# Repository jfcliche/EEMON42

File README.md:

# EEMON42
ESP32-C3-based 42-channel home energy monitor using the Analog Device ADE7816 emergy monitor chip

Features

  - 42 Current monitoring inputs with 3.5 mm jacks for current transformers
  - Single board, 10x10 cm design with OLED screen with a OLED/switch/rotary encoder user interface
  - Two AC voltage for split phase voltage monitoring and board powering
  - Micropython control software with MQTT telemetry streamed over WiFi

# Status

  V0 Hardware
    - Board is built. 
    - Hardware validation:
      - Switcher works. Board can be powered via USB or AC jacks. 
      - Can operate the ESP32 via the USB and micropython. 
      - All buttons work.
      - OLED display works
      - Only one ADE7816 is populated so far, but we can read registers.
    - Todo: 
      - Check analog inputs of ADE7816. Populate rest of the board. Calibrate all inputs.

  Software
    - Building basic micropyton modules
    - Todo: 
      - Implement main loop and monitoring/GUI tasks as coroutines. Improve display functions. Integrate with Home Assistant.

# Design Details:
- Accurate Energy monitoring performed by seven ADE7816
  - ESP32-C3 controller implemented with a Espressif ESP32-C3-WROOM-02 or AI Thinker ESP-C3-13 module, providing 
      - Single core RISC-V 160 MHz processor
      - 4 MB flash
      - Wifi, Bluetooth
      - Embedded USB controller
  - 96x64 pixel, 0.96" OLED display
  - 3 pushbutton keys 
  - Rotary encoder with integrated push button
  - Dual 9-15VAC inputs for line voltage monitoring and powering the board
  - Micro-USB connector for UART programming and JTAG debugging, and alternate board powering      
  - Integrated DC-DC converter for wide input voltage range

# Rationale

The EEMON42 was developed as personal project for learning all the steps to build an embedded controller project from A to Z, starting from from schematics & layout, online PCB manufacturing, hand soldering of high density SMD devices, an developing the embedded controller software. More specifically, this includes:

   - Learn KiCAD 6.0 and learn to place and route designs
   - Use PCBWay or JLCPCB to manufacture the PCB
   - Learn SMD soldering techniques for sizes down to 0603 and QFN 0.5mm pitch devices
   - Learn the internal architecture of the ESP32-C3-based module
   - Software development tools (Visual Studio Code / Platform IO / ESP IDF/ Micropython etc)

# History

2022/06: Design start
2022/12: Board was manufactured by PCBJLC. Board is assembled. Preliminary hardware verification is performed: power, ESP32, buttons and OLED display works with Micropython. Discovered bug in esptool that prevent the flashing stub to operate when USB-enabled micropython has booted first.
2023/03: ADE7816 is installed. Successful communication with it. Implement Python object for it. Implement SPI object to handle SPI CS pins shared with buttons and pin interrupts.

# Known bugs & gotcha's:

v1 hardware:
  - GPIO9 can be pull down and prevent micropython boot if encoder is left in mid-position
  - Missing GPIO2 & GPIO8 pullup (but still works without those)
  - A reset switch would be nice, but is becoming les and less necessary as hardware matures
  - A power LED would prevent accidental soldering on a powered board...
  - Pad and copper pour cleareaces too small close to USB connector: rookie solderers might cause shorts when applying too much solder...
  - serial number chip (or some GPIO strapping) might be useful for software to identify the hardware automatically. rev2 GPIOs assignments will change.  
  - encoder is a bit too close to screen for big fingers. Buttons should be spread out more.
  - Find socket with proper height for screen.

# Changelog:

 v2 hardware (under development):
  - OLED CS7 is now on FSPICS0 for native hardware-enabled CS toggling (if possible)
  - Encoder Button CS2 is on GPIO9 to prevent unwanted boot mode and allow user-controlled to force downnloader boot (although USB interface does not need it except for esptool bug)
  - CS0 and CS1 moved to other GPIOs
  - Added weak pullups on GPIO2 and GPIO8 to be sure

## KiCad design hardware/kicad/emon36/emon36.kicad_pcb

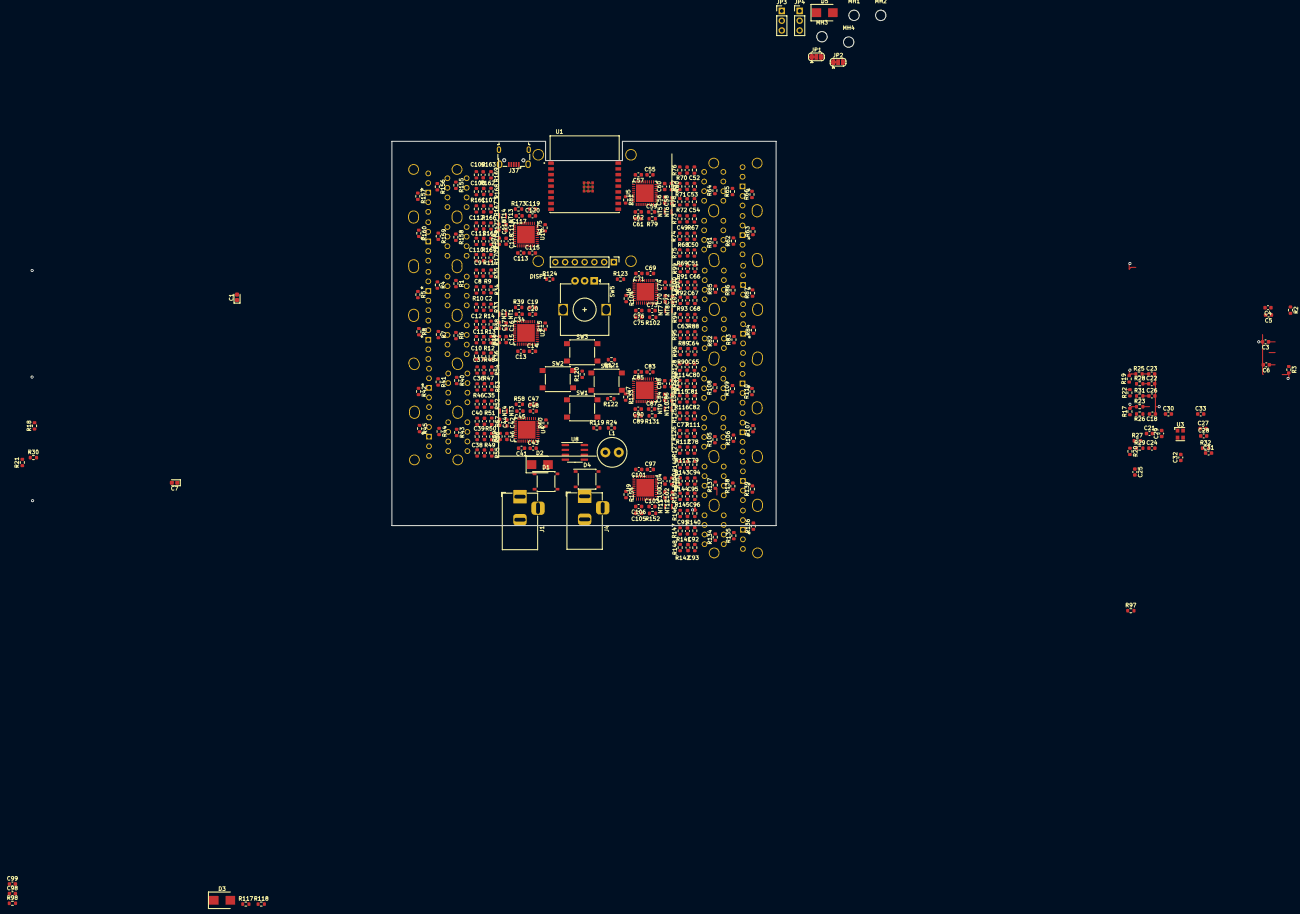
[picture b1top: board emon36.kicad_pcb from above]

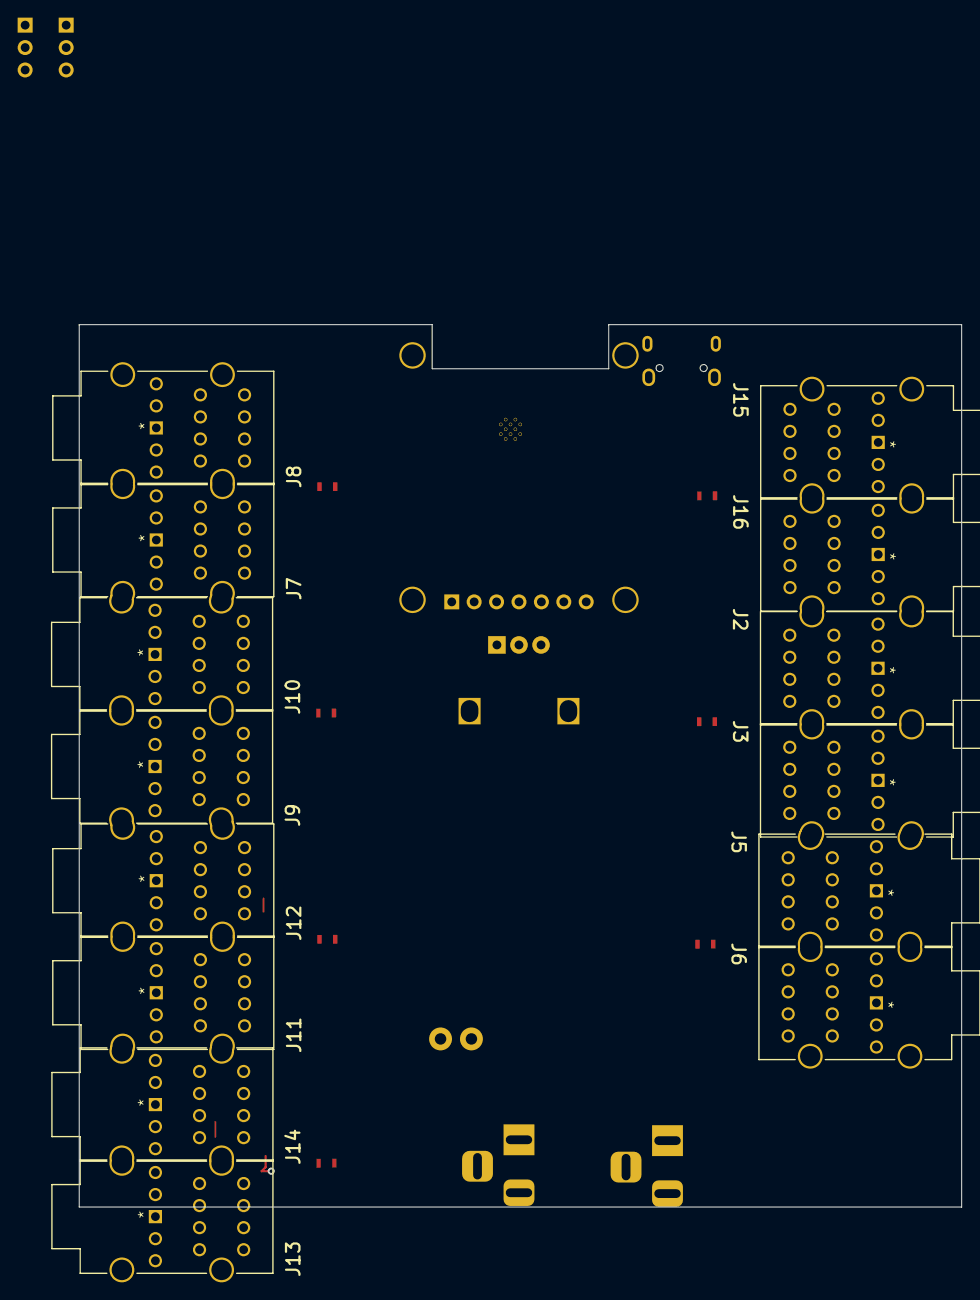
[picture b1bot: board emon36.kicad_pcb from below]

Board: 4 copper layers, 100.0 x 100.0 mm, 356 parts (14 on the bottom side), 197 nets.

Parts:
C1: 680uF/35V; CP_EIA-1608-08_AVX-J
C2, C8, C9, C10, C11, C12, C15, C34, C35, C36, C37, C38, C39, C40, C45, C46, C49, C50, C51, C52, C53, C54, C59, C60, C63, C64, C65, C66, C67, C68, C73, C74, C77, C78, C79, C80, C81, C82, C87, C88, C91, C92, C93, C94, C95, C96, C103, C104, C107, C108, C109, C110, C111, C112, C117, C118: 22nF; C_0603_1608Metric
C3, C6: 10uF/25V; C_0603_1608Metric
C4: 2.2nF; C_0603_1608Metric
C5, C18, C21, C22, C23, C26, C27, C28, C29: 10nF; C_0603_1608Metric
C7: 220uF/25V; CP_EIA-1608-08_AVX-J
C13, C16, C19, C24, C41, C42, C47, C55, C56, C61, C69, C70, C75, C83, C84, C89, C97, C100, C105, C113, C114, C119: 4.7uF; C_0603_1608Metric
C14, C20, C25, C43, C48, C57, C62, C71, C76, C85, C90, C101, C106, C115, C120: 0.22uF; C_0603_1608Metric
C17, C44, C58, C72, C86, C102, C116: 0.1uF; C_0603_1608Metric
C30, C31, C32, C33: 1uF/35V; C_0603_1608Metric
C98, C99: 22pF; C_0603_1608Metric
D1, D4: ABS6; Diode_Bridge_Diotec_ABS
D2, D3, D5: B240; D_SMB
DISP1: SSD1331_RGB_OLED_94x64; SSD1331_RGB_OLED_96x64
J1, J4: Barrel_Jack; BarrelJack_Horizontal
J2, J3, J5, J6, J7, J8, J9, J10, J11, J12, J13, J14, J15, J16: STX-4335-5BGP-S1; STX-4335-5BGP-S1_KYC
J37: USB_B_Micro; USB_Micro-B_Wuerth_629105150521
JP1, JP2: SolderJumper_3_Bridged12; SolderJumper-3_P1.3mm_Bridged12_RoundedPad1.0x1.5mm
JP3, JP4: Jumper_3_Bridged12; PinHeader_1x03_P2.54mm_Vertical
L1: 82uH; L_Radial_D7.5mm_P3.50mm_Fastron_07P
MH1, MH2, MH3, MH4: MountingHole; MountingHole_2.7mm_M2.5
NT1, NT2, NT3, NT4, NT5, NT6, NT7, NT8, NT9, NT10, NT11, NT12, NT13, NT14: NetTie_2; NetTie-2_SMD_Pad0.5mm
R1, R4, R5, R6, R7, R8, R40, R41, R42, R43, R44, R45, R61, R62, R63, R64, R65, R66, R82, R83, R84, R85, R86, R87, R105, R106, R107, R108, R109, R110, R134, R135, R136, R137, R138, R139, R155, R156, R157, R158, R159, R160: RB; R_0603_1608Metric
R2, R97, R98: 0; R_0603_1608Metric
R3: 47k; R_0603_1608Metric
R9, R10, R11, R12, R13, R14, R16, R39, R46, R47, R48, R49, R50, R51, R58, R59, R67, R68, R69, R70, R71, R72, R79, R80, R88, R89, R90, R91, R92, R93, R102, R103, R111, R112, R113, R114, R115, R116, R131, R132, R140, R141, R142, R143, R144, R145, R152, R153, R161, R162, R163, R164, R165, R166, R173, R174: 1k; R_0603_1608Metric
R15, R60, R81, R104, R133, R154, R175: 22; R_0603_1608Metric
R17, R18, R19, R20, R21, R22, R117, R118: 75; R_0603_1608Metric
R23: 2.2K; R_0603_1608Metric
R24, R119, R120, R121, R122, R123, R124: 2.2k; R_0603_1608Metric
R25, R26, R27, R28: 21.5K; R_0603_1608Metric
R29, R30, R31, R32, R33, R34, R35, R36, R37, R38, R52, R53, R54, R55, R56, R57, R73, R74, R75, R76, R77, R78, R94, R95, R96, R99, R100, R101, R125, R126, R127, R128, R129, R130, R146, R147, R148, R149, R150, R151, R167, R168, R169, R170, R171, R172: 499; R_0603_1608Metric
SW1, SW2, SW3, SW4: SW_MEC_5E; SW_Push_1P1T_NO_6x6mm_H13mm
SW5: RotaryEncoder; RotaryEncoder_Alps_EC12E_Vertical_H20mm
U1: ESP32-C3-WROOM-02-N4; MODULE_ESP32-C3-WROOM-02-H4
U2, U4, U5, U6, U7, U9, U10: QFN-40-1EP_6x6mm_P0.5mm_EP4.6x4.6mm
U3: 16.384MHz; Oscillator_SMD_Kyocera_KC2520Z-4Pin_2.5x2.0mm
U8: TPS54233; SOIC-8_3.9x4.9mm_P1.27mm

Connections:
3V3: C7.1, C24.1, C25.1, D5.2 (A), DISP1.2 (VCC), J37.1 (VBUS), L1.2, R23.1, U1.1 (3V3), U2.2 (PULL_HIGH), U2.26 (VDD), U3.4 (VCC), U4.2 (PULL_HIGH), U4.26 (VDD), U5.2 (PULL_HIGH), U5.26 (VDD), U6.2 (PULL_HIGH), U6.26 (VDD), U7.2 (PULL_HIGH), U7.26 (VDD), U8.5 (FB), U9.2 (PULL_HIGH), U9.26 (VDD), U10.2 (PULL_HIGH), U10.26 (VDD)
/CH0/IABC_N: C107.2, C108.2, C109.2, J15.1, NT13.1, R155.2, R156.2, R157.2, R167.2, R168.2, R169.2
/CH0/IA_P: C107.1, R161.2, R167.1, U10.7 (IAP)
/CH0/IB_P: C108.1, R162.2, R168.1, U10.9 (IBP)
/CH0/IC_P: C109.1, R163.2, R169.1, U10.13 (ICP)
/CH0/IDEF_N: C110.2, C111.2, C112.2, J16.1, NT14.1, R158.2, R159.2, R160.2, R170.2, R171.2, R172.2
/CH0/ID_P: C110.1, R164.2, R170.1, U10.23 (IDP)
/CH0/IE_P: C111.1, R165.2, R171.1, U10.22 (IEP)
/CH0/IF_P: C112.1, R166.2, R172.1, U10.19 (IFP)
/CH1/IABC_N: C2.2, C8.2, C9.2, J2.1, NT1.1, R1.2, R4.2, R5.2, R33.2, R34.2, R35.2
/CH1/IA_P: C2.1, R10.2, R33.1, U2.7 (IAP)
/CH1/IB_P: C8.1, R9.2, R34.1, U2.9 (IBP)
/CH1/IC_P: C9.1, R11.2, R35.1, U2.13 (ICP)
/CH1/IDEF_N: C10.2, C11.2, C12.2, J3.1, NT2.1, R6.2, R7.2, R8.2, R36.2, R37.2, R38.2
/CH1/ID_P: C10.1, R12.2, R36.1, U2.23 (IDP)
/CH1/IE_P: C11.1, R13.2, R37.1, U2.22 (IEP)
/CH1/IF_P: C12.1, R14.2, R38.1, U2.19 (IFP)
/CH2/IABC_N: C35.2, C36.2, C37.2, J5.1, NT3.1, R40.2, R41.2, R42.2, R52.2, R53.2, R54.2
/CH2/IA_P: C35.1, R46.2, R52.1, U4.7 (IAP)
/CH2/IB_P: C36.1, R47.2, R53.1, U4.9 (IBP)
/CH2/IC_P: C37.1, R48.2, R54.1, U4.13 (ICP)
/CH2/IDEF_N: C38.2, C39.2, C40.2, J6.1, NT4.1, R43.2, R44.2, R45.2, R55.2, R56.2, R57.2
/CH2/ID_P: C38.1, R49.2, R55.1, U4.23 (IDP)
/CH2/IE_P: C39.1, R50.2, R56.1, U4.22 (IEP)
/CH2/IF_P: C40.1, R51.2, R57.1, U4.19 (IFP)
/CH3/IABC_N: C49.2, C50.2, C51.2, J7.1, NT5.1, R61.2, R62.2, R63.2, R73.2, R74.2, R75.2
/CH3/IA_P: C49.1, R67.2, R73.1, U5.7 (IAP)
/CH3/IB_P: C50.1, R68.2, R74.1, U5.9 (IBP)
/CH3/IC_P: C51.1, R69.2, R75.1, U5.13 (ICP)
/CH3/IDEF_N: C52.2, C53.2, C54.2, J8.1, NT6.1, R64.2, R65.2, R66.2, R76.2, R77.2, R78.2
/CH3/ID_P: C52.1, R70.2, R76.1, U5.23 (IDP)
/CH3/IE_P: C53.1, R71.2, R77.1, U5.22 (IEP)
/CH3/IF_P: C54.1, R72.2, R78.1, U5.19 (IFP)
/CH4/IABC_N: C63.2, C64.2, C65.2, J9.1, NT7.1, R82.2, R83.2, R84.2, R94.2, R95.2, R96.2
/CH4/IA_P: C63.1, R88.2, R94.1, U6.7 (IAP)
/CH4/IB_P: C64.1, R89.2, R95.1, U6.9 (IBP)
/CH4/IC_P: C65.1, R90.2, R96.1, U6.13 (ICP)
/CH4/IDEF_N: C66.2, C67.2, C68.2, J10.1, NT8.1, R85.2, R86.2, R87.2, R99.2, R100.2, R101.2
/CH4/ID_P: C66.1, R91.2, R99.1, U6.23 (IDP)
/CH4/IE_P: C67.1, R92.2, R100.1, U6.22 (IEP)
/CH4/IF_P: C68.1, R93.2, R101.1, U6.19 (IFP)
/CH5/IABC_N: C77.2, C78.2, C79.2, J11.1, NT9.1, R105.2, R106.2, R107.2, R125.2, R126.2, R127.2
/CH5/IA_P: C77.1, R111.2, R125.1, U7.7 (IAP)
/CH5/IB_P: C78.1, R112.2, R126.1, U7.9 (IBP)
/CH5/IC_P: C79.1, R113.2, R127.1, U7.13 (ICP)
/CH5/IDEF_N: C80.2, C81.2, C82.2, J12.1, NT10.1, R108.2, R109.2, R110.2, R128.2, R129.2, R130.2
/CH5/ID_P: C80.1, R114.2, R128.1, U7.23 (IDP)
/CH5/IE_P: C81.1, R115.2, R129.1, U7.22 (IEP)
/CH5/IF_P: C82.1, R116.2, R130.1, U7.19 (IFP)
/CH6/IABC_N: C91.2, C92.2, C93.2, J13.1, NT11.1, R134.2, R135.2, R136.2, R146.2, R147.2, R148.2
/CH6/IA_P: C91.1, R140.2, R146.1, U9.7 (IAP)
/CH6/IB_P: C92.1, R141.2, R147.1, U9.9 (IBP)
/CH6/IC_P: C93.1, R142.2, R148.1, U9.13 (ICP)
/CH6/IDEF_N: C94.2, C95.2, C96.2, J14.1, NT12.1, R137.2, R138.2, R139.2, R149.2, R150.2, R151.2
/CH6/ID_P: C94.1, R143.2, R149.1, U9.23 (IDP)
/CH6/IE_P: C95.1, R144.2, R150.1, U9.22 (IEP)
/CH6/IF_P: C96.1, R145.2, R151.1, U9.19 (IFP)
/CLK16MHZ: R17.1, R18.1, R19.1, R20.1, R21.2, U2.27 (CLKIN), U4.27 (CLKIN), U5.27 (CLKIN), U6.27 (CLKIN), U7.27 (CLKIN), U9.27 (CLKIN), U10.27 (CLKIN)
/IRQ: R24.2, U2.29 (*IRQ0), U2.32 (*IRQ1), U4.29 (*IRQ0), U4.32 (*IRQ1), U5.29 (*IRQ0), U5.32 (*IRQ1), U6.29 (*IRQ0), U6.32 (*IRQ1), U7.29 (*IRQ0), U7.32 (*IRQ1), U9.29 (*IRQ0), U9.32 (*IRQ1), U10.29 (*IRQ0), U10.32 (*IRQ1)
/OLED_C/~D: DISP1.6 (D/~C), U1.17 (GPIO1_ADC1CH1_XTAL32N)
/OLED_RES: DISP1.5 (~RES), U1.18 (GPIO0_ADC1CH0_XTAL32P)
/RESET: C29.1, R23.2, U1.2 (EN), U2.4 (~RESET), U4.4 (~RESET), U5.4 (~RESET), U7.4 (~RESET), U9.4 (~RESET), U10.4 (~RESET)
/SPI_CS0: R123.1, U1.10 (GPIO10_FSPICS0), U10.39 (*SS/HAS)
/SPI_CS1: R124.1, U1.8 (GPIO9), U2.39 (*SS/HAS)
/SPI_CS2: R119.1, U1.7 (GPIO8), U4.39 (*SS/HAS)
/SPI_CS3: R120.1, U1.15 (GPIO3_ADC1CH3), U5.39 (*SS/HAS)
/SPI_CS4: R121.1, U1.4 (GPIO5_ADC2CH0_FSPIWP_MTDI), U6.39 (*SS/HAS)
/SPI_CS5: R122.1, U1.3 (GPIO4_ADC1_CH4_FSPIHD_MTMS), U7.39 (*SS/HAS)
/SPI_CS6: R24.1, U1.12 (GPIO21_UART0TXD), U9.39 (*SS/HAS)
/SPI_CS7: DISP1.7 (~CS), U1.11 (GPIO20_UART0RXD)
/SPI_MISO: R15.2, R22.1, R60.2, R81.2, R104.2, R133.2, R154.2, R175.2, U1.16 (GPIO2_ADC1CH2_FSPIQ)
/SPI_MOSI: DISP1.4 (SDA), R118.1, U1.6 (GPIO7_FSPID_MTDO), U2.38 (MOSI/SDA), U4.38 (MOSI/SDA), U5.38 (MOSI/SDA), U6.38 (MOSI/SDA), U7.38 (MOSI/SDA), U9.38 (MOSI/SDA), U10.38 (MOSI/SDA)
/SPI_SCLK: DISP1.3 (SCL), R117.1, U1.5 (GPIO6_FSPICLK_MTCK), U2.36 (SCLK/SCL), U4.36 (SCLK/SCL), U5.36 (SCLK/SCL), U6.36 (SCLK/SCL), U7.36 (SCLK/SCL), U9.36 (SCLK/SCL), U10.36 (SCLK/SCL)
/USB_D+: C99.1, J37.3 (D+), R98.1
/USB_D-: C98.1, J37.2 (D-), R97.1
/VA+: JP3.1 (A), R25.2, R29.1, U2.15 (VP), U4.15 (VP), U5.15 (VP), U10.15 (VP)
/VA-: JP4.1 (A), R26.2, R30.2, U2.16 (VN), U4.16 (VN), U5.16 (VN), U10.16 (VN)
/VB+: JP3.2 (C), U6.15 (VP), U7.15 (VP), U9.15 (VP)
/VB-: JP4.2 (C), U6.16 (VN), U7.16 (VN), U9.16 (VN)
/VBI+: JP3.3 (B), R27.2, R31.1
/VBI-: JP4.3 (B), R28.2, R32.2
GND: C1.2, C3.2, C4.2, C5.2, C7.2, C13.2, C14.2, C15.2, C16.2, C17.2, C18.2, C19.2, C20.2, C21.2, C22.2, C23.2, C24.2, C25.2, C26.2, C27.2, C28.2, C29.2, C34.2, C41.2, C42.2, C43.2, C44.2, C45.2, C46.2, C47.2, C48.2, C55.2, C56.2, C57.2, C58.2, C59.2, C60.2, C61.2, C62.2, C69.2, C70.2, C71.2, C72.2, C73.2, C74.2, C75.2, C76.2, C83.2, C84.2, C85.2, C86.2, C87.2, C88.2, C89.2, C90.2, C97.2, C98.2, C99.2, C100.2, C101.2, C102.2, C103.2, C104.2, C105.2, C106.2, C113.2, C114.2, C115.2, C116.2, C117.2, C118.2, C119.2, C120.2, D2.2 (A), DISP1.1 (GND), J37.5 (GND), JP1.2 (C), JP2.2 (C), NT1.2, NT2.2, NT3.2, NT4.2, NT5.2, NT6.2, NT7.2, NT8.2, NT9.2, NT10.2, NT11.2, NT12.2, NT13.2, NT14.2, R2.2, R16.1, R29.2, R30.1, R31.2, R32.1, R39.1, R58.1, R59.1, R79.1, R80.1, R102.1, R103.1, R131.1, R132.1, R152.1, R153.1, R173.1, R174.1, SW5.C, U1.9 (GND), U1.19 (GND), U1.20 (GND), U1.21 (GND), U1.22 (GND), U1.23 (GND), U1.24 (GND), U1.25 (GND), U1.26 (GND), U1.27 (GND), U2.1 (NC_4), U2.3 (PULL_LOW), U2.6 (DGND), U2.10 (NC_6), U2.11 (NC_8), U2.20 (NC_10), U2.21 (NC_2), U2.25 (AGND), U2.30 (NC_3), U2.31 (NC_5), U2.40 (NC), U2.41 (EP(AGND)), U3.2 (GND), U4.1 (NC_4), U4.3 (PULL_LOW), U4.6 (DGND), U4.10 (NC_6), U4.11 (NC_8), U4.20 (NC_10), U4.21 (NC_2), U4.25 (AGND), U4.30 (NC_3), U4.31 (NC_5), U4.40 (NC), U4.41 (EP(AGND)), U5.1 (NC_4), U5.3 (PULL_LOW), U5.6 (DGND), U5.10 (NC_6), U5.11 (NC_8), U5.20 (NC_10), U5.21 (NC_2), U5.25 (AGND), U5.30 (NC_3), U5.31 (NC_5), U5.40 (NC), U5.41 (EP(AGND)), U6.1 (NC_4), U6.3 (PULL_LOW), U6.6 (DGND), U6.10 (NC_6), U6.11 (NC_8), U6.20 (NC_10), U6.21 (NC_2), U6.25 (AGND), U6.30 (NC_3), U6.31 (NC_5), U6.40 (NC), U6.41 (EP(AGND)), U7.1 (NC_4), U7.3 (PULL_LOW), U7.6 (DGND), U7.10 (NC_6), U7.11 (NC_8), U7.20 (NC_10), U7.21 (NC_2), U7.25 (AGND), U7.30 (NC_3), U7.31 (NC_5), U7.40 (NC), U7.41 (EP(AGND)), U8.7 (GND), U9.1 (NC_4), U9.3 (PULL_LOW), U9.6 (DGND), U9.10 (NC_6), U9.11 (NC_8), U9.20 (NC_10), U9.21 (NC_2), U9.25 (AGND), U9.30 (NC_3), U9.31 (NC_5), U9.40 (NC), U9.41 (EP(AGND)), U10.1 (NC_4), U10.3 (PULL_LOW), U10.6 (DGND), U10.10 (NC_6), U10.11 (NC_8), U10.20 (NC_10), U10.21 (NC_2), U10.25 (AGND), U10.30 (NC_3), U10.31 (NC_5), U10.40 (NC), U10.41 (EP(AGND))
unnamed: C1.1, D1.1 (+), D3.2 (A), D4.1 (+)
unnamed: C3.1, D3.1 (K), D5.1 (K), U8.2 (VIN)
unnamed: C4.1, R3.2
unnamed: C5.1, U8.4 (SS)
unnamed: C6.1, U8.1 (BOOT)
unnamed: C6.2, D2.1 (K), L1.1, U8.8 (PH)
unnamed: C18.1, C21.1, C22.1, C23.1, R17.2, R18.2, R19.2, R20.2
unnamed: C28.1, R22.2
unnamed: C30.1, R25.1
unnamed: C30.2, D1.4, J1.1
unnamed: C31.1, D1.3, J1.2, JP1.3 (B)
unnamed: C31.2, R26.1
unnamed: C32.1, R27.1
unnamed: C32.2, D4.4, J4.1
unnamed: C33.1, D4.3, J4.2, JP2.3 (B)
unnamed: C33.2, R28.1
unnamed: C41.1, C43.1, U4.24 (AVDD)
unnamed: C42.1, C44.1, U4.17 (REFIN/OUT)
unnamed: C45.1, R58.2, U4.8 (IAN), U4.12 (IBN), U4.14 (ICN)
unnamed: C46.1, R59.2, U4.18 (IN)
unnamed: C47.1, C48.1, U4.5 (DVDD)
unnamed: C55.1, C57.1, U5.24 (AVDD)
unnamed: C56.1, C58.1, U5.17 (REFIN/OUT)
unnamed: C59.1, R79.2, U5.8 (IAN), U5.12 (IBN), U5.14 (ICN)
unnamed: C60.1, R80.2, U5.18 (IN)
unnamed: C61.1, C62.1, U5.5 (DVDD)
unnamed: C69.1, C71.1, U6.24 (AVDD)
unnamed: C70.1, C72.1, U6.17 (REFIN/OUT)
unnamed: C73.1, R102.2, U6.8 (IAN), U6.12 (IBN), U6.14 (ICN)
unnamed: C74.1, R103.2, U6.18 (IN)
unnamed: C75.1, C76.1, U6.5 (DVDD)
unnamed: C83.1, C85.1, U7.24 (AVDD)
unnamed: C84.1, C86.1, U7.17 (REFIN/OUT)
unnamed: C87.1, R131.2, U7.8 (IAN), U7.12 (IBN), U7.14 (ICN)
unnamed: C88.1, R132.2, U7.18 (IN)
unnamed: C89.1, C90.1, U7.5 (DVDD)
unnamed: C100.1, C102.1, U9.17 (REFIN/OUT)
unnamed: C97.1, C101.1, U9.24 (AVDD)
unnamed: C103.1, R152.2, U9.8 (IAN), U9.12 (IBN), U9.14 (ICN)
unnamed: C104.1, R153.2, U9.18 (IN)
unnamed: C105.1, C106.1, U9.5 (DVDD)
unnamed: C113.1, C115.1, U10.24 (AVDD)
unnamed: C114.1, C116.1, U10.17 (REFIN/OUT)
unnamed: C117.1, R173.2, U10.8 (IAN), U10.12 (IBN), U10.14 (ICN)
unnamed: C118.1, R174.2, U10.18 (IN)
unnamed: C119.1, C120.1, U10.5 (DVDD)
unnamed: D1.2 (-), JP1.1 (A)
unnamed: D4.2 (-), JP2.1 (A)
unnamed: J2.5, R5.1, R11.1
unnamed: J2.25, R4.1, R9.1
unnamed: J2.35, R1.1, R10.1
unnamed: J3.5, R8.1, R14.1
unnamed: J3.25, R7.1, R13.1
unnamed: J3.35, R6.1, R12.1
unnamed: J5.5, R42.1, R48.1
unnamed: J5.25, R41.1, R47.1
unnamed: J5.35, R40.1, R46.1
unnamed: J6.5, R45.1, R51.1
unnamed: J6.25, R44.1, R50.1
unnamed: J6.35, R43.1, R49.1
unnamed: J7.5, R63.1, R69.1
unnamed: J7.25, R62.1, R68.1
unnamed: J7.35, R61.1, R67.1
unnamed: J8.5, R66.1, R72.1
unnamed: J8.25, R65.1, R71.1
unnamed: J8.35, R64.1, R70.1
unnamed: J9.5, R84.1, R90.1
unnamed: J9.25, R83.1, R89.1
unnamed: J9.35, R82.1, R88.1
unnamed: J10.5, R87.1, R93.1
unnamed: J10.25, R86.1, R92.1
unnamed: J10.35, R85.1, R91.1
unnamed: J11.5, R107.1, R113.1
unnamed: J11.25, R106.1, R112.1
unnamed: J11.35, R105.1, R111.1
unnamed: J12.5, R110.1, R116.1
unnamed: J12.25, R109.1, R115.1
unnamed: J12.35, R108.1, R114.1
unnamed: J13.5, R136.1, R142.1
unnamed: J13.25, R135.1, R141.1
unnamed: J13.35, R134.1, R140.1
unnamed: J14.5, R139.1, R145.1
unnamed: J14.25, R138.1, R144.1
unnamed: J14.35, R137.1, R143.1
unnamed: J15.5, R157.1, R163.1
unnamed: J15.25, R156.1, R162.1
unnamed: J15.35, R155.1, R161.1
unnamed: J16.5, R160.1, R166.1
unnamed: J16.25, R159.1, R165.1
unnamed: J16.35, R158.1, R164.1
unnamed: R2.1, U8.3 (EN)
unnamed: R3.1, U8.6 (COMP)
unnamed: R15.1, U2.37 (MISO/HSD)
unnamed: C15.1, R16.2, U2.18 (IN)
unnamed: R21.1, U3.3 (CLK)
unnamed: R60.1, U4.37 (MISO/HSD)
unnamed: R81.1, U5.37 (MISO/HSD)
unnamed: R97.2, U1.13 (GPIO18_USB-)
unnamed: R98.2, U1.14 (GPIO19_USB+)
unnamed: R104.1, U6.37 (MISO/HSD)
unnamed: C26.1, R117.2
unnamed: C27.1, R118.2
unnamed: R119.2, SW1.1, SW1.2
unnamed: R120.2, SW2.1, SW2.2
unnamed: R121.2, SW3.1, SW3.2
unnamed: R122.2, SW4.1, SW4.2
unnamed: R123.2, SW5.A
unnamed: R124.2, SW5.B
unnamed: R133.1, U7.37 (MISO/HSD)
unnamed: R154.1, U9.37 (MISO/HSD)
unnamed: R175.1, U10.37 (MISO/HSD)
unnamed: C19.1, C20.1, U2.5 (DVDD)
unnamed: C34.1, R39.2, U2.8 (IAN), U2.12 (IBN), U2.14 (ICN)
unnamed: C16.1, C17.1, U2.17 (REFIN/OUT)
unnamed: C13.1, C14.1, U2.24 (AVDD)

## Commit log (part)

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2022-09-03 First commit if the schematics and pcb
2022-09-03 Added 3D models in LFS
2022-09-04 Added symbol and 3d_model for Digilent PModOLED, and symbol only for PmodOledrgb
2022-09-04 Added some info in README
2022-09-05 Added Digilent PmodOLEDrgb footprint with rough 3d model
2022-09-10 Add preliminary USB interface
2022-09-10 Add tactile switch footprint and 3d model
2022-09-11 Reverted to stacked 3.5mm connectors. Now has 42 channels. Added OLED, switches, power system. Cleaned up channel page.
2022-09-11 schematics: Added todo list, 2nd AC connector, series caps to SPI terminations.
2022-10-14 Added .gitignore and .gitattribute (for LFS)
2022-10-14 Another major schematics/PCB iteration. Added decoupling caps, interrupts, etc. Improved power system. Added clock.
2022-12-03 Finished schematics, layout and routing. Ready for verification.
2022-12-05 Added lots of silkscreen info. Added silk clearance and JLCPCB stackup. Improved Dc-DC with copper pours. Added SPI testpoints.
2022-12-06 Schematics: completed/updated some part number fields. Changed 4.7uF to 16V for better effective capacitance. Cleanup top sheet.
2022-12-08 Added IRQ diodes - ADE7816 IRQs not open collector. Added pin 1 markers. Increased track widths. Cleanup. Made OLED mounting holes non plated.
2022-12-08 Fixed VBUS copper pour
2022-12-09 Added an optional pullup resistor in case the internal one is not strong enough to boas all the IRQ diodes.
2022-12-16 Added diodes on IRQ, included solder mask and silk constraints, fix silk. Version sent to production.
2022-12-16 Added production gerber (LFS)
2022-12-16 Renamed files to EEMON42
2022-12-16 Renamed emon36 folder to eemon42
2022-12-31 Update README.md
    Updated README for new repo name and status
2022-12-31 Added preliminary python files used to test the OLED display from the computer
2023-01-26 Add MQTT counter with OLED support
2023-01-26 Fix OLED not drawing properly
2023-01-26 Add rotary encoder handling
2023-02-01 Add simulator and text input
2023-03-04 Added e2_spi.py with SPI_with_CS class to handle dual-function CS pins. Adapted ade7816 to micropython and new SPI interface.
2023-03-04 Schematics update: Added pullups on GPIO2 & 8. Shuffles CS lines so OLED CS7 is on FSPICS0 (for native toggling), CS2 is on GPO9 so encoder button can control boot mode. CS0 and CS1 are displaced.
2023-03-04 Updated README status & changelog
2023-03-05 Added home-made rotary switch handler. Updated test() method
2023-03-06 e42_rotary2.py: re-thought the rotary encoder decoding algorithm, which is now more robust. Tweaked the SPI_with_CS API, using preallocated buffers for speed. Use buffers for ADE7816 read/write_reg (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
2023-03-14 Simulation code in separate directory and integration of new rotary encoder
2023-03-27 sim: renamed Display to ssd1331. Modified so it can be used by main code. Added method to set the surface objects after creation.
2023-03-27 sim: renamed rotary to rotary_encoder. Modified so it can be used directly my main code.
2023-03-27 sim: button: Modified so it can be used by main code directly. Added method to set rectangle.
2023-03-27 sim: ade7816: added emulator code (does nothing for now)
2023-03-27 sim: added basic machine and network modules to allow the micropython code to run on a PC.
2023-03-27 spi: renamed e42_spi to spi. dual-use pins are now passed as a list, not a dict. All methods should pass the CS pin object, not device name. Updated irq wrapper: now only wraps, does not set IRQ. Add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
2023-03-27 ade7816: support new spi API.
2023-03-27 rotary_encoder: renamed from e42_rotary2. Now sets pin IRQ, with optional wrapper function.
2023-03-27 ssd1331: renamed from display.py. Supports new spi API.
2023-03-27 sim: gitignore: ignore user config file
2023-03-27 gitignore: ignore IDE folders
2023-03-27 gui: Implement menu system as coroutine. Moved test_input() menu as a gui method (becomes shorter and more efficient).
2023-03-27 eemon42.py: renamed from main.py. Refactor using classes and asyncio. Wifi & MQTT are now background processes running concurrently with the gui coroutine. Handled cancellation and keyboard interrupt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
2023-03-27 sim: main: refactored simulator to use coroutines and new factored code. Simplify some code. Completely uses the original micropython code. Added library overrides and display/button post-init config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
2023-03-27 umqttsimple: attempt to make it compatible with Cpython. Currently have errors when trying to connect to Mosquitto
2023-03-27 Bunch of fixes.
2023-03-29 spi: added a SPI.deinit() before creating a new SPI object, otherwise the port does not work.
2023-03-29 ssd1331: placed display init in separate method.
2023-03-29 Moved display init from gui.run() to eemon42.__init__() so we know if the board is alive.
2023-03-29 button: Added IRQ wrapper for the button. Used a irq to detect when button is pressed. button is not functional: need new code to debounce and properly increment _value.
2023-03-30 boot: start eemon42 application if we hold button C at boot.
2023-03-30 button: implemented IRQ-baes basic debouncing. not perfect. Removed unused code.
2023-03-31 sim: pass the surface variable to the SSD1331 class so it is available during EEMON42.__init__ to initialize the simulated display
2023-03-31 button: implement a better debouncing algorithm that does not require a Timer.
2023-04-02 Cleanup button code
2023-04-02 eemon42: add screen saver
2023-04-02 Add frame buffer and optimize display
2024-09-23 feat (ssd1331): cleanup, move higher-level frame buffer functions to display module.
2024-09-23 feat (display): added generic framebuffer/display module. Moved in print functions. Added 5x7 font.
2024-09-23 feat (ade7816): better handling of reg data formats. Implement init(), interrpt handling, current/voltage/energy calib. energy accumulation. Uses linecycle energy readout mode..
2024-09-23 feat (boot): commeted out unused code
2024-09-23 feat (eemon42): separated __init__() from init() code. Implemented energy readout on all energy moitor ICs
2024-09-23 fix (sims): updated simulated device code to match latest architecture
2024-09-23 docs: Updated README and added cheat sheet
2024-10-08 build: Added a pymakr config file
2024-10-08 feat (display): added brightness, line drawing. Normalize font handling. Optimize.
2024-10-08 feat (rotary): added shift-rotate.
2024-10-08 feat (ade7816): Added line-cycle integ and apparent and reactive energy
2024-10-08 feat (main): make main module attributes available to the REPL (__main__)
2024-10-08 feat (boot): remove code from boot as it is normally used for low level init.
2024-10-08 feat (gui): Normalize button functions, simplify and add shift-rorate to edit_box, added list_box.
2024-10-08 feat (eemon42): Added pin interrupt on IRQ with ThreadSafeflag, added screen saver, improve emon readout loop.
2024-10-08 feat (sim): added simulation features to support updated new micropython code
2024-10-08 feat (sim): parametrize graphics. Remove init() from __init__().
2024-10-08 build (pymakr): Updated config
